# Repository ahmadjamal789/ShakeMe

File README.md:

# ShakeMe

A handheld, battery-powered display that behaves like a solute in a solvent. Left at rest, the particles on screen settle to the bottom. Shake or move it, and they are kicked up and spread through the whole volume. When the motion stops, they slowly resettle.

Built for **Hack Club, Week 4: Displays Week** ("Design with Displays").

<p align="center">

  <br><em>The finished device.</em>
</p>

## The idea

A motion sensor measures how hard the device is being disturbed, and that measurement drives a particle simulation drawn on a color TFT.

- **At rest:** gravity wins and the particles settle into a layer, like sediment.
- **Disturbed:** the acceleration reading becomes an "agitation" value that gives the particles random kicks, so they disperse rapidly.
- **After the disturbance:** agitation decays over time and the particles slowly resettle.

## Status

- [x] Concept and parts chosen
- [x] Schematic drawn in KiCad
- [x] Custom symbols, footprints and 3D models for the display, IMU, charger and battery
- [ ] PCB layout (in progress)
- [ ] Firmware
- [ ] Enclosure

## Hardware

| Part | Choice | Notes |
|---|---|---|
| Microcontroller | Raspberry Pi Pico (RP2040) | Powered through VSYS |
| Display | ST7789 2.0" 240x320 SPI TFT | 3.3 V logic, 8-pin header |
| Motion sensor | MPU6050 breakout (8-pin) | I2C, 3.3 V, on-board regulator and pull-ups |
| Battery | 3.7 V LiPo, 500 to 1000 mAh, with protection board | Pouch cell no larger than the Pico (21 x 51 mm) |
| Charger | TP4056 Type-C module (with protection) | Charges the battery over USB-C |
| Power switch | Slide switch | Between the battery and the Pico |
| Diode | Schottky, SOD-123 | Battery to VSYS, so USB and battery don't fight |
| Controls | Two tactile buttons | Mode and spare |
| Passives | 10 uF bulk capacitor on VSYS, 100 nF decoupling on 3.3 V | Plus backlight MOSFET and resistors if the display needs them |

### Power

```
USB-C -> TP4056 -> LiPo (protected) -> slide switch -> Schottky diode -> Pico VSYS
                                                                        |
                                              Pico 3V3(OUT) -> display, IMU
```

- The TP4056 module charges the cell from its own USB-C port. Switch the device off while charging.
- The Pico's own regulator makes the 3.3 V rail, so no separate regulator is used.
- VBUS is left unconnected. The Pico's USB port powers it internally when plugged in.

### Pin assignments

Planned mapping. Update this table to match the final schematic.

| Signal | Pico pin |
|---|---|
| Display DC / CS / SCL / SDA / RES / BLK | GP0 / GP1 / GP2 / GP3 / GP4 / GP5 |
| IMU SDA / SCL | See schematic (I2C pair) |
| IMU AD0 | GND (address 0x68) |
| Buttons | See schematic |

## PCB design

All design work was done in KiCad. The three modules that have no stock library parts (display, IMU, charger) and the LiPo cell outline use custom symbols, footprints and 3D models, kept in `hardware/DisplaysWeek/`.

### Schematic

<p align="center">

  <br><em>Figure 1. Full schematic.</em>
</p>

The schematic is split into five blocks:

- **Power:** battery connector, TP4056 charger, slide switch, Schottky diode to VSYS, 10 uF bulk capacitor.
- **Controller:** Pico, with the 3.3 V rail taken from its 3V3(OUT) pin and decoupled with 100 nF.
- **Display:** ST7789 on hardware SPI, with the backlight driven directly or through a MOSFET depending on the module.
- **Motion:** MPU6050 on I2C.
- **Controls:** two tactile buttons.

### Board layout

<p align="center">

  <br><em>Figure 2. Full board layout, all layers visible.</em>
</p>

- **Board:** 2 layers, [width] x [height] mm.
- **Placement:** [describe which parts sit on the front and which on the back once the layout is final].
- **Pin tails:** through-hole header pins come out on the opposite face. Each header has a keep-out rule area on the other side, so nothing sits where its tails land. The display header's tails are kept clear of the Pico, whose underside has exposed test pads, and of the battery.
- **Battery:** the cell is a courtyard-only footprint with no pads. No tails and no tall parts sit under it.
- **Traces:** about 0.5 mm for VSYS and the battery path, about 0.25 mm for signals, with a GND pour on both sides and stitching vias.
- **IMU placement:** kept away from the charger, which warms up while charging.

### 3D render

| Front | Back |
|---|---|
|  |  |
| *Figure 5. 3D render, front.* | *Figure 6. 3D render, back.* |

Rendered with KiCad's 3D viewer using the custom STEP models.

### Final 3D model

<p align="center">
 
  <br><em>Figure 7. Final 3D model of the assembled device.</em>
</p>

### Manufacturing files

- Gerbers and drill files: `hardware/gerbers/` (add when generated)
- Bill of materials: `hardware/bom.csv` (add when generated)

## Repository layout (suggested)

```
hardware/
  kicad/                  KiCad project (schematic and PCB)
  DisplaysWeek/           custom symbol, footprint and 3D libraries
  gerbers/                manufacturing files
firmware/                 Pico firmware
docs/
  images/                 pictures used in this README
README.md
```

## Firmware plan

- C++ with the Arduino-Pico core and PlatformIO.
- Display: TFT_eSPI or LovyanGFX over hardware SPI.
- IMU: any MPU6050 library; subtract gravity and take the acceleration magnitude.
- Physics loop each frame:
  1. Read acceleration and low-pass filter it.
  2. Update agitation: `E = max(E * decay, |a|)`.
  3. For each particle: apply gravity, add a random kick scaled by `E`, apply drag, bounce off the walls.
- Optional: use the gravity vector so particles slosh when the device is tilted.

## Design notes and known issues

- **Through-hole pin tails:** header pins come out on the opposite side of the board. Keep them clear of other parts, and never let them touch the battery or the Pico's underside test pads. Clip them flush after soldering and cover with Kapton tape.
- **Backlight:** some ST7789 modules take BLK as a logic input, others use it as the LED cathode. Test the module before deciding whether the MOSFET is needed.
- **LiPo polarity:** many cells use the opposite polarity to the standard JST connector. Check the cell's red and black wires against the connector before plugging in.
- **Module sizes:** the footprints use typical dimensions. Measure the real modules before ordering boards.

## Safety

LiPo cells can catch fire if shorted, punctured, over-charged or over-discharged. Use a cell with a protection board, never charge it unattended while testing, and stop using it if the pouch swells.

## Credits

Built for Hack Club Displays Week. Designed in KiCad.

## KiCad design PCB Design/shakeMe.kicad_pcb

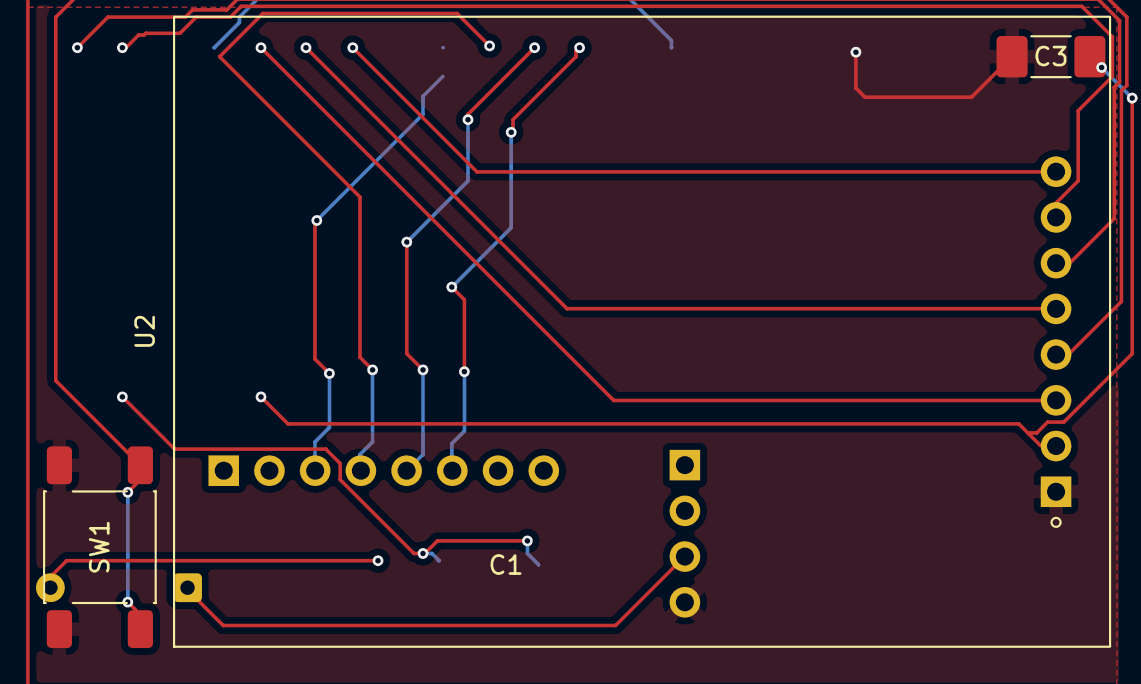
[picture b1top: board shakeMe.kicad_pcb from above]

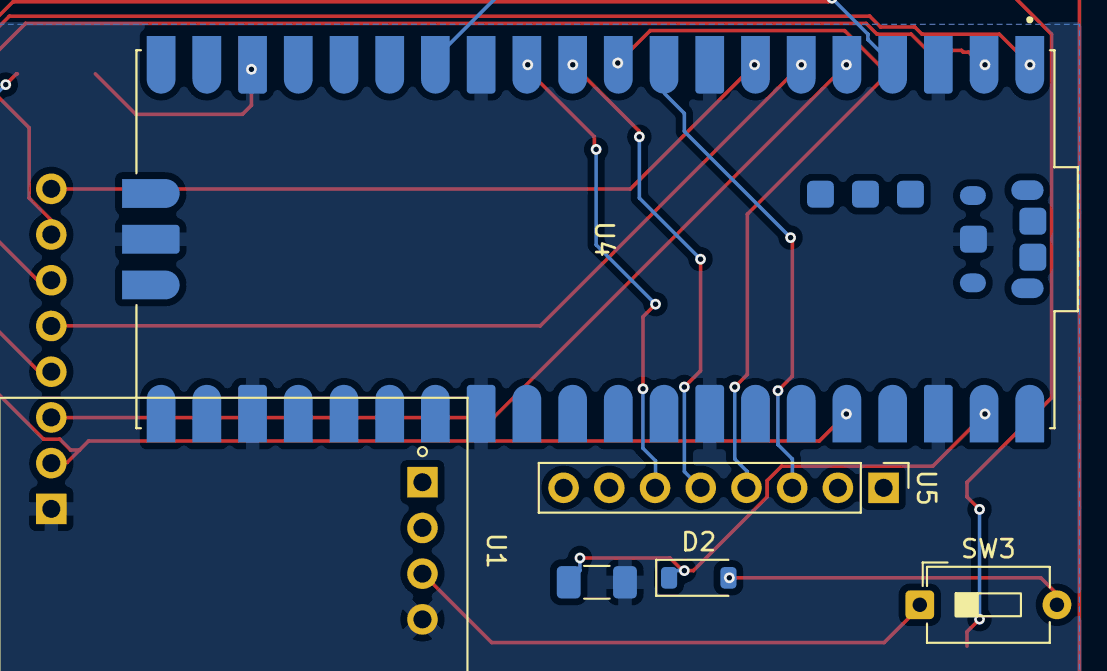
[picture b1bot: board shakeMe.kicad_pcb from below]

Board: 2 copper layers, 9 parts (6 on the bottom side), 16 nets.

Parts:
C1: 10uF, 10V; C_1206_3216Metric_Pad1.33x1.80mm_HandSolder
C3: 100nF; C_1808_4520Metric_Pad1.72x2.30mm_HandSolder
D2: BAT42W-V; D_SOD-123
SW1: SW_Push; SW_Push_1P1T_NO_E-Switch_TL3301NxxxxxG
SW3: Power_sw; SW_DIP_SPSTx01_Slide_6.7x4.1mm_W7.62mm_P2.54mm_LowProfile
U1: TP4056_TypeC; Charger_TP4056_TypeC_Protected
U2: ST7789_2.0_TFT; Display_ST7789_2in_8pin
U4: SC0917; MODULE_SC0917
U5: MPU6050; PinHeader_1x08_P2.54mm_Vertical

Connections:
+3.3V: C3.2, U2.2 (VCC), U4.36 (3V3_OUT)
GND: C1.2, C3.1, SW1.1, U1.4 (OUT-), U2.1 (GND), U4.3 (GND), U4.8 (GND), U4.13 (GND), U4.18 (GND), U4.23 (GND), U4.28 (GND), U4.33 (AGND), U4.38 (GND), U4.D2 (GND), U4.TP1 (TP1_GND)
unnamed: D2.2 (A), SW3.2 (B)
unnamed: C1.1, D2.1 (K), U4.39 (VSYS)
unnamed: SW3.1 (A), U1.3 (OUT+)
unnamed: U2.8 (BLK), U4.7 (GP5)
unnamed: U2.7 (CS), U4.2 (GP1)
unnamed: U2.6 (DC), U4.1 (GP0)
unnamed: U2.5 (RES), U4.6 (GP4)
unnamed: U2.3 (SCL), U4.5 (GP3)
unnamed: U2.4 (SDA), U4.4 (GP2)
unnamed: U4.9 (GP6), U5.3 (SCL)
unnamed: U4.10 (GP7), U5.4 (SDA)
unnamed: U4.11 (GP8), U5.5 (XDA)
unnamed: U4.12 (GP9), U5.6 (XCL)
unnamed: SW1.2, U4.14 (GP10)
